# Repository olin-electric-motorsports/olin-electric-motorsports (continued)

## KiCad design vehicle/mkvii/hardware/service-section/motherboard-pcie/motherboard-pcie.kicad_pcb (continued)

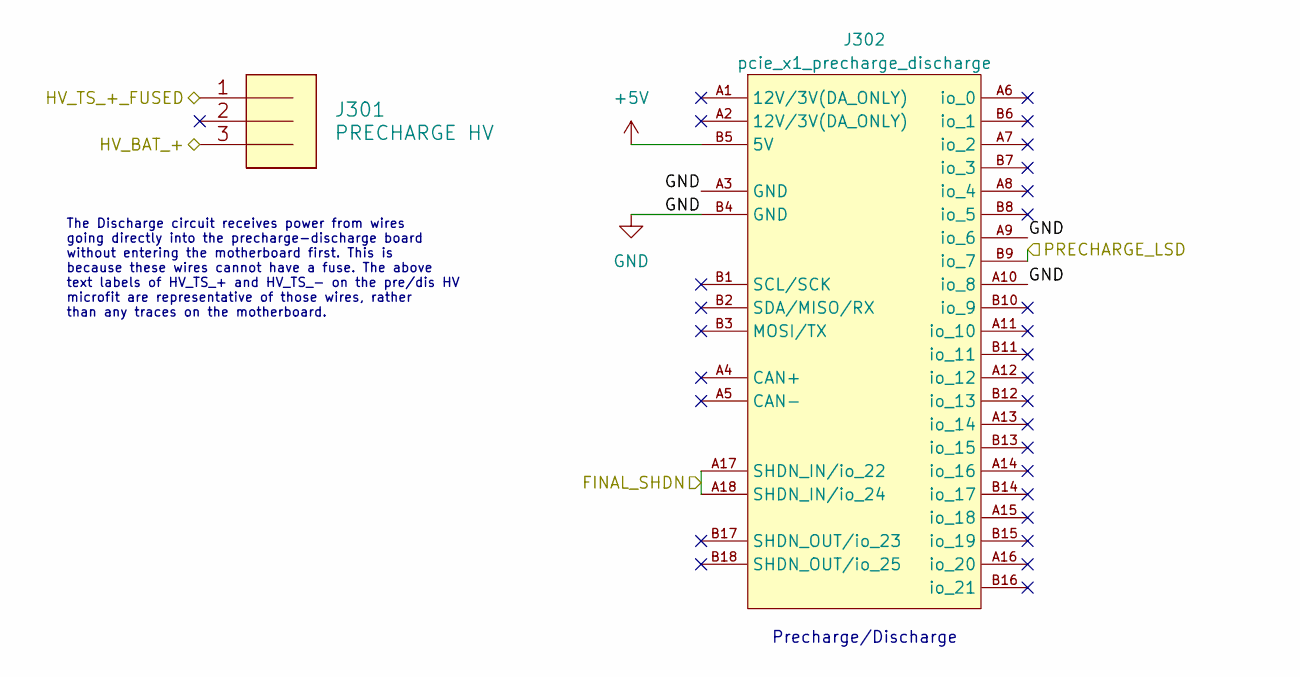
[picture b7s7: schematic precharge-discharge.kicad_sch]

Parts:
J301: PRECHARGE HV; MicroFit_VT_3; MPN 436500327
J302: pcie_x1_precharge_discharge; te_pcie_x1_connector

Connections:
+5V: J302.B5 (5V); also elsewhere on the board
/FINAL_SHDN: J302.A17 (SHDN_IN/io_22), J302.A18 (SHDN_IN/io_24); also elsewhere on the board
/HV_BAT_+: J301.3; also elsewhere on the board
/HV_TS_+_FUSED: J301.1; also elsewhere on the board
/PRECHARGE_LSD: J302.B9 (io_7); also elsewhere on the board
GND: J302.A3 (GND), J302.A9 (io_6), J302.A10 (io_8), J302.B4 (GND); also elsewhere on the board

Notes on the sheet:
Precharge/Discharge
The Discharge circuit receives power from wires going directly into the precharge-discharge board without entering the motherboard first. This is because these wires cannot have a fuse. The above text labels of HV_TS_+ and HV_TS_- on the pre/dis HV microfit are representative of those wires, rather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

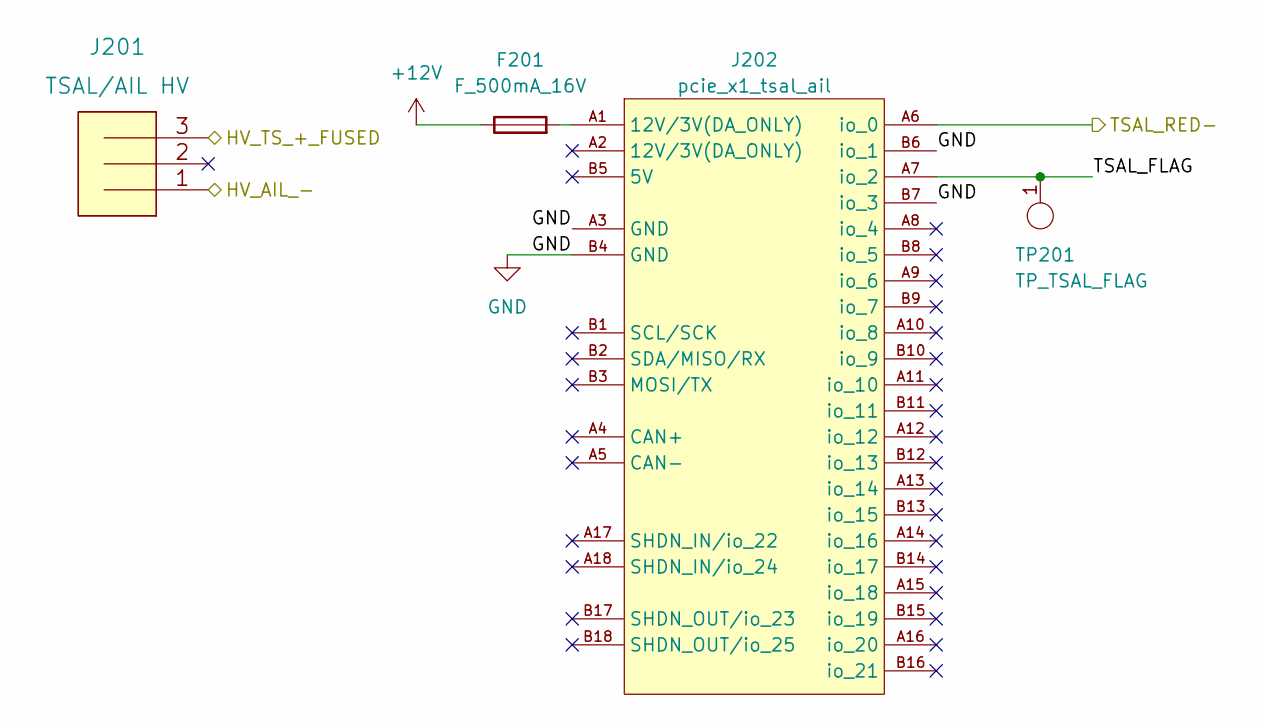
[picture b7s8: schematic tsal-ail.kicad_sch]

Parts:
F201: F_500mA_16V; Fuse_1210; MPN 0ZCH0050FF2G
J201: TSAL/AIL HV; MicroFit_VT_3; MPN 436500327
J202: pcie_x1_tsal_ail; te_pcie_x1_connector
TP201: TP_TSAL_FLAG; TestPoint_Pad_D1.0mm

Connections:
+12V: F201.1; also elsewhere on the board
/HV_AIL_-: J201.1; also elsewhere on the board
/HV_TS_+_FUSED: J201.3; also elsewhere on the board
/TSAL_RED-: J202.A6 (io_0); also elsewhere on the board
/tsal-ail/TSAL_FLAG: J202.A7 (io_2), TP201.1
GND: J202.A3 (GND), J202.B4 (GND), J202.B6 (io_1), J202.B7 (io_3); also elsewhere on the board
unnamed: F201.2, J202.A1 (12V/3V(DA_ONLY))

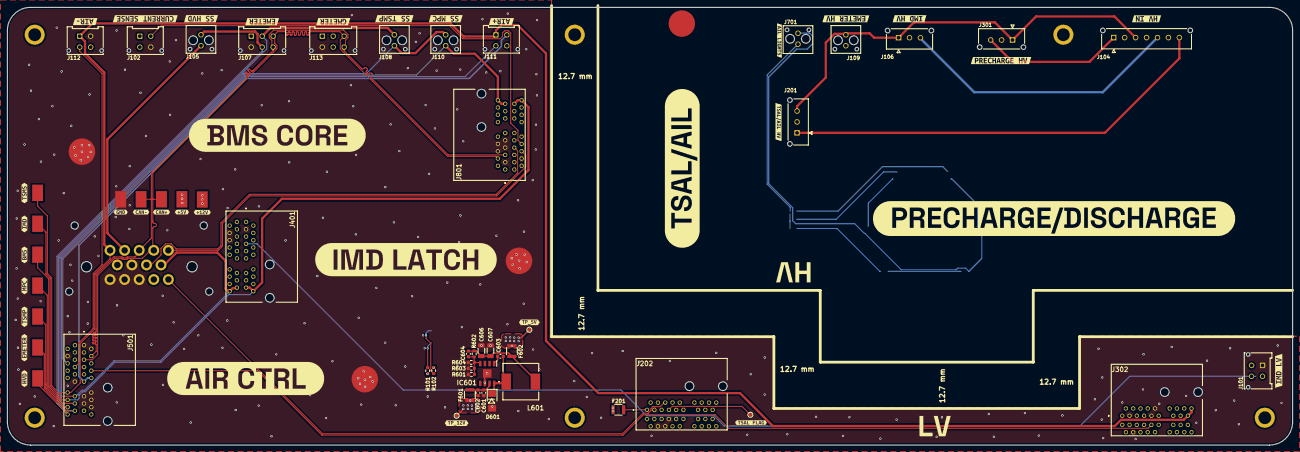
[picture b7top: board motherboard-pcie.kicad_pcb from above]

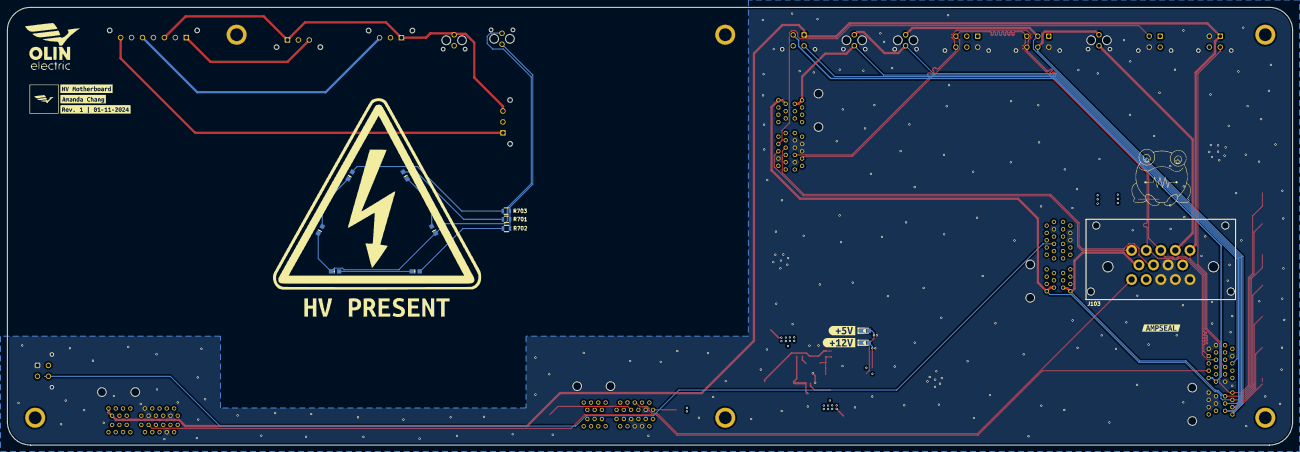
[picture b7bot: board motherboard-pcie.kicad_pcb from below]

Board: 4 copper layers, 352.4 x 120.0 mm, 109 parts (19 on the bottom side), 43 nets.

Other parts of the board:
kibuzzard-640B75B2: G***; kibuzzard-640B75B2
kibuzzard-640B76B0: G***; kibuzzard-640B76B0
kibuzzard-640B87CD: G***; kibuzzard-640B87CD
kibuzzard-640B861F: G***; kibuzzard-640B861F
kibuzzard-640B8645: G***; kibuzzard-640B8645
kibuzzard-640B8668: G***; kibuzzard-640B8668
kibuzzard-640B8680: G***; kibuzzard-640B8680
kibuzzard-677B3C3E: G***; kibuzzard-677B3C3E
kibuzzard-677B3C38: G***; kibuzzard-677B3C38
kibuzzard-677B3E90: G***; kibuzzard-677B3E90
kibuzzard-677CE749: G***; kibuzzard-677CE749
kibuzzard-677CFB84: G***; kibuzzard-677CFB84
kibuzzard-677CFB97: G***; kibuzzard-677CFB97
kibuzzard-677CFBA0: G***; kibuzzard-677CFBA0
kibuzzard-677E2BD4: G***; kibuzzard-677E2BD4
kibuzzard-677E2BDC: G***; kibuzzard-677E2BDC
kibuzzard-677E2BE2: G***; kibuzzard-677E2BE2
kibuzzard-677E2BE7: G***; kibuzzard-677E2BE7
kibuzzard-677E2BEC: G***; kibuzzard-677E2BEC
kibuzzard-677E2BF5: G***; kibuzzard-677E2BF5
kibuzzard-677E2BFE: G***; kibuzzard-677E2BFE
kibuzzard-677E26A9: G***; kibuzzard-677E26A9
kibuzzard-677E26B0: G***; kibuzzard-677E26B0
kibuzzard-677E26B5: G***; kibuzzard-677E26B5
kibuzzard-677E26BE: G***; kibuzzard-677E26BE
kibuzzard-677E26C5: G***; kibuzzard-677E26C5
kibuzzard-677E26CB: G***; kibuzzard-677E26CB
kibuzzard-677E26D4: G***; kibuzzard-677E26D4
kibuzzard-677E26ED: G***; kibuzzard-677E26ED
kibuzzard-677E335B: G***; kibuzzard-677E335B
kibuzzard-677E336E: G***; kibuzzard-677E336E
kibuzzard-677E3331: G***; kibuzzard-677E3331
kibuzzard-677E3355: G***; kibuzzard-677E3355
kibuzzard-677E3368: G***; kibuzzard-677E3368
kibuzzard-677FDCF4: G***; kibuzzard-677FDCF4
kibuzzard-67822EAD: G***; kibuzzard-67822EAD
kibuzzard-67822EC1: G***; kibuzzard-67822EC1
kibuzzard-678236F4: G***; kibuzzard-678236F4
kibuzzard-678238A8: G***; kibuzzard-678238A8
kibuzzard-678249D1: G***; kibuzzard-678249D1
kibuzzard-678249DC: G***; kibuzzard-678249DC
kibuzzard-6782498C: G***; kibuzzard-6782498C
kibuzzard-67823702: G***; kibuzzard-67823702
kibuzzard-67823719: G***; kibuzzard-67823719

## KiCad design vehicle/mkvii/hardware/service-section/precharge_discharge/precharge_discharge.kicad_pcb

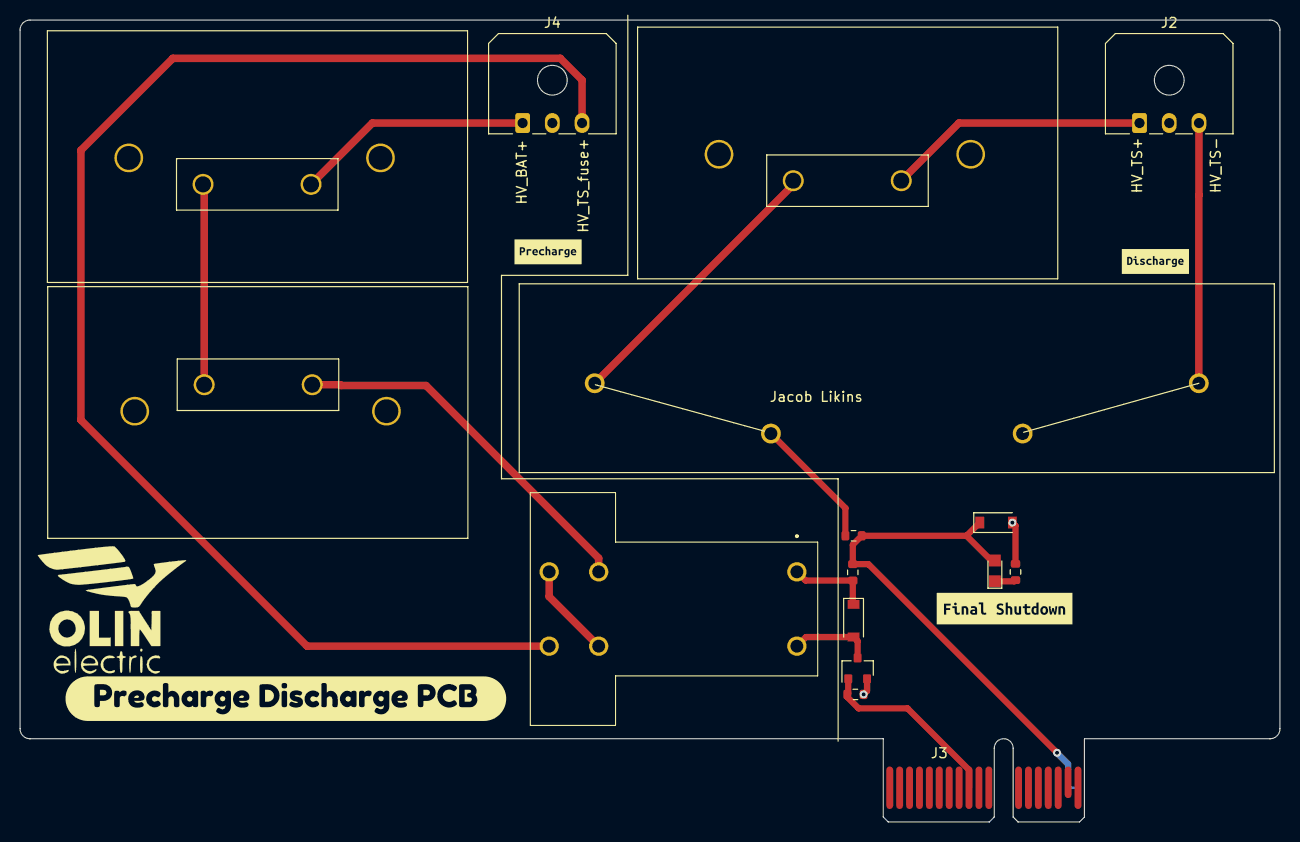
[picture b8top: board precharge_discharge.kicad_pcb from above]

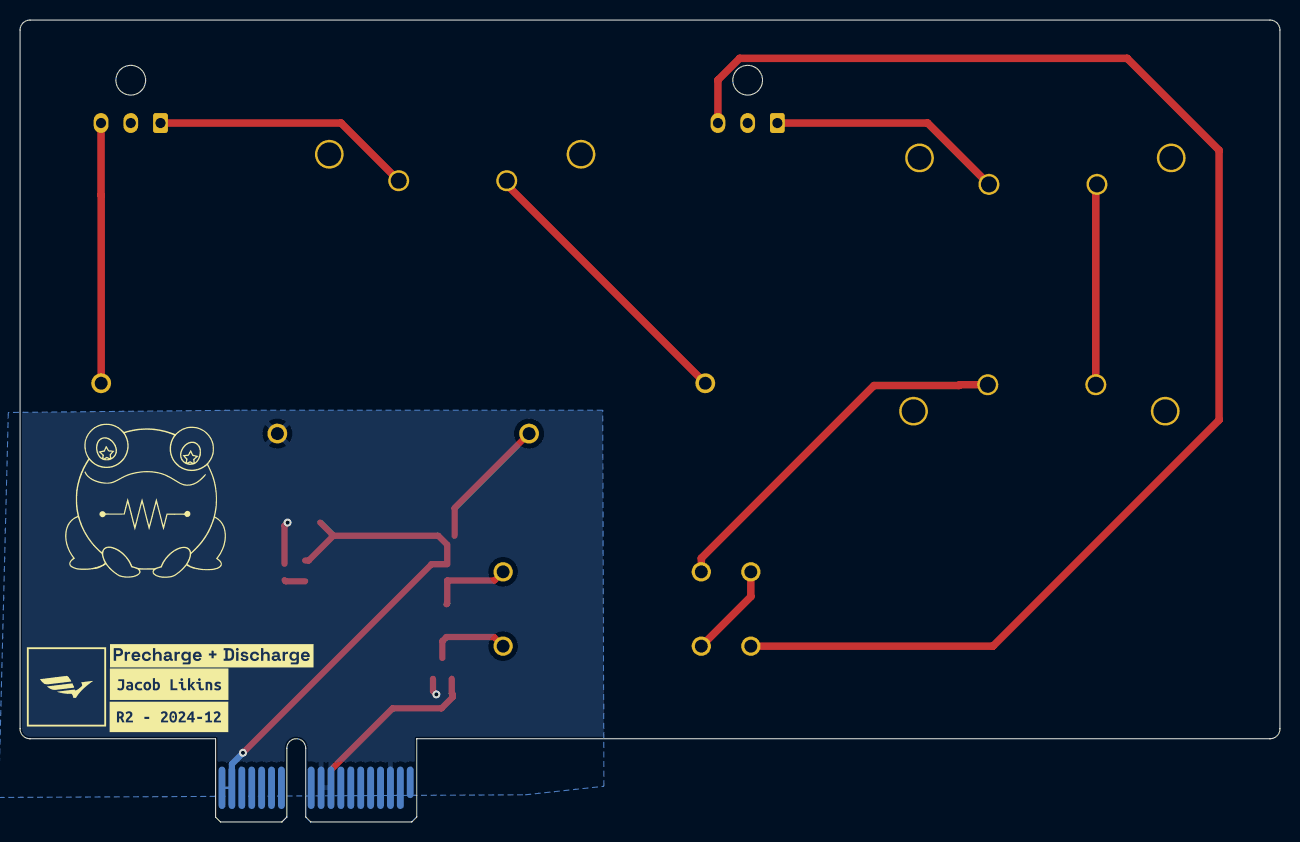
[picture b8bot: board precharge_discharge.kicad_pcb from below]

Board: 2 copper layers, 127.1 x 80.9 mm, 26 parts (6 on the bottom side), 15 nets.

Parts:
D1, D3: SS110LW; D_SOD-123
D2: LED_WHITE; CHIPLED_0805
G1: LOGO; star
G2: LOGO; fromis
G3: LOGO; kirbystar2
J2, J4: Conn_01x03_Pin; Molex_Micro-Fit_3.0_43650-0300_1x03_P3.00mm_Horizontal
J3: CONN_pcie_x1; pcie_x1
K1: G2RG-2A-X_DC12; G2RG-X
K2: 3350-4275-126; Relay_Comus_3350
Q1: SSM3K333R; SOT-23F
R1: 10KR; R_0603
R2, R5: 12R; R_0603
R3, R4: 560R-100W; R_TO247-Heatsink
R6: 3KR-100W; R_TO247-Heatsink
R7: 1KR; R_0603
kibuzzard-63D8409B: G***; kibuzzard-63D8409B
kibuzzard-6758D9E9: G***; kibuzzard-6758D9E9
kibuzzard-6758DA0D: G***; kibuzzard-6758DA0D
kibuzzard-67535F35: G***; kibuzzard-67535F35
kibuzzard-639639B8: G***; kibuzzard-639639B8
kibuzzard-67522083: G***; kibuzzard-67522083
kibuzzard-67522094: G***; kibuzzard-67522094

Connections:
/FINAL_SHUTDOWN: D2.2 (A), D3.1 (K), J3.A17 (SHDN_IN/io_22), J3.A18 (SHDN_IN/io_24), R2.1, R5.1
/HV_BAT+: J4.1, R4.2
/HV_TS+: J2.1, R6.2
/HV_TS+_Fuse: J4.3, K1.5 (NO_(-))
/HV_TS-: J2.3, K2.4
/PRECHARGE_LSD: J3.B9 (io_7), Q1.1 (G), R1.1
GND: D3.2 (A), J3.A3 (GND), J3.A9 (io_6), J3.A10 (io_8), J3.B4 (GND), K2.3 (-), Q1.2 (S), R1.2, R7.2
unnamed: D1.2 (A), K1.8 (COIL_2), Q1.3 (D)
unnamed: D1.1 (K), K1.1 (COIL_1), R2.2
unnamed: D2.1 (K), R7.1
unnamed: K1.4 (NO), K1.6 (COM)
unnamed: K1.3 (COM_(+)), R3.1
unnamed: K2.2 (+), R5.2
unnamed: K2.1, R6.1
unnamed: R3.2, R4.1
